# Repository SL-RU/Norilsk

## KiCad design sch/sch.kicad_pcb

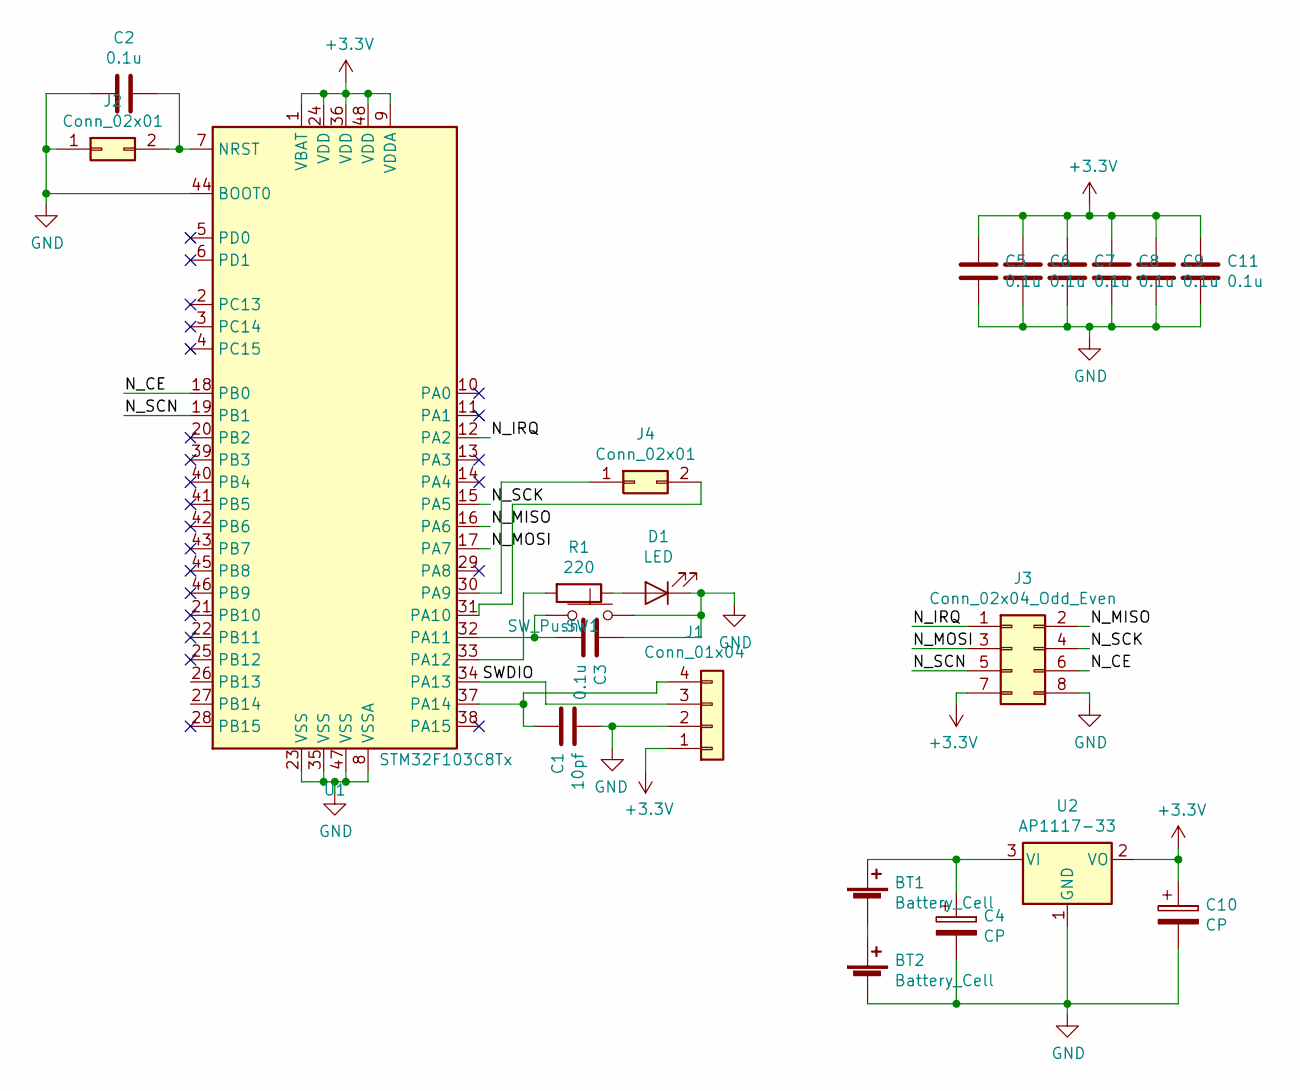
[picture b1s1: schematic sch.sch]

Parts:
BT1, BT2: Battery_Cell; BatteryHolder_Keystone_103_1x20mm
C1: 10pf; C_0603_1608Metric
C2, C3, C5, C6, C7, C8, C9, C11: 0.1u; C_0402_1005Metric
C4, C10: CP; CP_Radial_D5.0mm_P2.50mm
D1: LED; LED_D3.0mm
J1: Conn_01x04; PinHeader_1x04_P2.54mm_Vertical
J2, J4: Conn_02x01; PinHeader_2x01_P1.27mm_Vertical_SMD
J3: Conn_02x04_Odd_Even; PinHeader_2x04_P2.54mm_Vertical
R1: 220; R_0603_1608Metric
SW1: SW_Push; SW_SPST_B3SL-1002P
U1: STM32F103C8Tx; LQFP-48_7x7mm_P0.5mm
U2: AP1117-33; SOT-223-3_TabPin2

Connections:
+3V3: C5.1, C6.1, C7.1, C8.1, C9.1, C10.1, C11.1, J1.1, J3.7, U1.1 (VBAT), U1.9 (VDDA), U1.24 (VDD), U1.36 (VDD), U1.48 (VDD), U2.2 (VO)
/N_CE: J3.6, U1.18 (PB0)
/N_IRQ: J3.1, U1.12 (PA2)
/N_MISO: J3.2, U1.16 (PA6)
/N_MOSI: J3.3, U1.17 (PA7)
/N_SCK: J3.4, U1.15 (PA5)
/N_SCN: J3.5, U1.19 (PB1)
/SWDIO: J1.3, U1.34 (PA13)
GND: BT2.2 (-), C1.2, C2.2, C3.1, C4.2, C5.2, C6.2, C7.2, C8.2, C9.2, C10.2, C11.2, D1.1 (K), J1.2, J2.1, J3.8, SW1.2, U1.8 (VSSA), U1.23 (VSS), U1.35 (VSS), U1.44 (BOOT0), U1.47 (VSS), U2.1 (GND)
unnamed: BT1.1 (+), C4.1, U2.3 (VI)
unnamed: BT1.2 (-), BT2.1 (+)
unnamed: C1.1, J1.4, U1.37 (PA14)
unnamed: C2.1, J2.2, U1.7 (NRST)
unnamed: C3.2, SW1.1, U1.32 (PA11)
unnamed: D1.2 (A), R1.1
unnamed: J4.1, U1.30 (PA9)
unnamed: J4.2, U1.31 (PA10)
unnamed: R1.2, U1.33 (PA12)

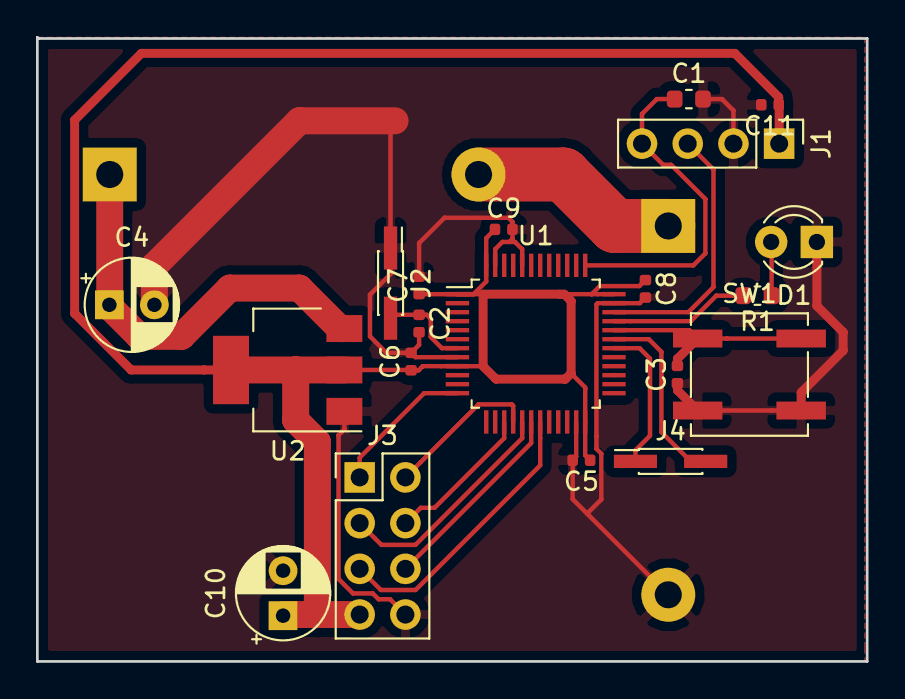
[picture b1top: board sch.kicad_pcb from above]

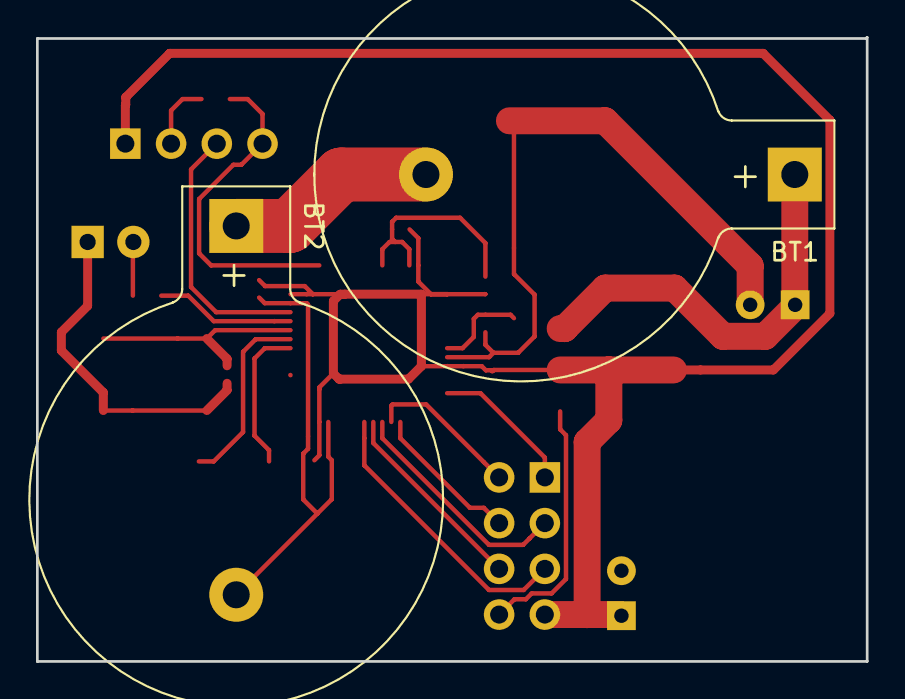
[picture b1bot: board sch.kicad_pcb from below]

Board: 2 copper layers, 46.1 x 34.7 mm, 22 parts (2 on the bottom side), 18 nets.

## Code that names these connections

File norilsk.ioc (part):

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Mcu.Name=STM32F103C(8-B)Tx
Mcu.Package=LQFP48
Mcu.UserName=STM32F103C8Tx
PA10.Mode=Asynchronous
PA10.Signal=USART1_RX
PA11.GPIOParameters=GPIO_Label
PA11.GPIO_Label=Button
PA11.Signal=GPIO_Input
PA12.GPIOParameters=GPIO_Label
PA12.GPIO_Label=LED
PA12.Signal=GPIO_Output
PA13.Mode=Serial_Wire
PA13.Signal=SYS_JTMS-SWDIO
PA14.Mode=Serial_Wire
PA14.Signal=SYS_JTCK-SWCLK
PA2.GPIOParameters=GPIO_Label
PA2.GPIO_Label=NRF_IRQ
PA2.Signal=GPXTI2
PA5.Mode=Full_Duplex_Master
PA5.Signal=SPI1_SCK
PA6.Mode=Full_Duplex_Master
PA6.Signal=SPI1_MISO
PA7.Mode=Full_Duplex_Master
PA7.Signal=SPI1_MOSI
PA9.Mode=Asynchronous
PA9.Signal=USART1_TX
PB0.GPIOParameters=GPIO_Label
PB0.GPIO_Label=NRF_CS
PB0.Signal=GPIO_Output
PB1.GPIOParameters=GPIO_Label
PB1.GPIO_Label=NRF_SCN
PB1.Signal=GPIO_Output
RCC.SYSCLKFreq_VALUE=64000000
RCC.SYSCLKSource=RCC_SYSCLKSOURCE_PLLCLK
board=custom

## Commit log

2018-12-14 NRF24 lib created and reformatted
2018-12-20 nrf on 411 ok
2018-12-21 Robot WIP
2018-12-24 nrf24 robot lib to RF24 arduino lib
2018-12-27 nrf24 transmit ok
2019-01-01 6 pults ready
